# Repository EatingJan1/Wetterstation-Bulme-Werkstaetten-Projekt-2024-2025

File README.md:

# Completed school project - archived
the project continues here: https://github.com/EatingJan1/BlueRubberDuck-Weatherstation

## Wetterstation-Bulme-Werkstätten-Projekt-2024/2025

#### Outdoor-Wetterstation
Sensoren:
- BME688: xyz
- UV-Strahlung 
- Luftdruck -> easy BME680(END OF LIVE)/BME688 ist bisl besser und gleiches PINOUT und kostet nur weniger 1€ teurer
- Luftpartikel -> gehackter von Ikea(belüftet Lüfter drin)
- Temperatur -> easy BME680(END OF LIVE)/BME688 ist bisl besser und gleiches PINOUT und kostet nur weniger 1€ teurer
- Regenmenge -> Kippwage & Regenitensität über Zeit
- Windrichtung
- Windgeschwindigkeit
- Bodenfeuchtigkeit 
- UV-Strahlung Winkel -> Berechnen durch von Geolocation
- Dezibel Messung (Optional, Eher nicht)
- Höhenlage -> GPS oder Luftdruck aber zählt eher zu Berchnungen
- CO2 gehalt

##### Belüftete Sensoren  -> Mit 5V Lüfter -> ideal ohne moglichkeit ohne Lüfter
- Temperatur
- Luftfeuchtigkeit
- CO2 Gehalt
- Luftdruck
- Luftpartikel -> gehackter von Ikea (Lüfter drin) -> Teurer es zu hacken / aus zu bauen wie einen Neuen zu Kaufen

##### Berechnung:
- Taupunkt
- kWh/m2 (Sonneneinstrahlung) -> Mehrere Sensoren notwendig zu aufwendig
- gefühlte Temperatur -> Wind + Temp +Sonneneinstrahlung Vielleicht Über temperatur direkt an der gehäusewand ob eher hohe Sonneneinstrahlung oder niedrige 
- Sichtweite -> Feinstaub wichtig 
- Photovoltaik für Outdoor -> Zu viele Variablen
- Windmessung über Ultraschalwandler

##### Funk:
Übertragung: Thread

#### Mini Station:

Misst alle Daten in einem Standard Indoor Raum

Gewollte Messung:
- Temperatur
- Luftfeuchtigkeit
- CO2 Gehalt
- Luftdruck
- Helligkeit (Photowiderstand)

##### Funk:
Übertragung: Thread

#### Daten Station (HUB)
Schittstelle zu unserer Datenbank und ins Local Area Network zur überwachung der Daten

- SD Karten speicherung
- Lan anstatt Wlan
- Lan Driver
- Power über POE
- Überträgt alle Messdaten der letzen seit dem Letzten Timestamp der Datenbank einmalig pro Tag auf unseren MySQL Server. (Welche möglichkeit bzw. Daten auf mehrere Server senden)
    - Server Jan:
        - Im Falle eines Ausfall -> Selbständige Lösung, jedoch Auafall wahrscheinlichkeit höher
        - Gefahr das Daten beschädigt werden / Gelöscht
        - Komplette Administration aller Daten und des Ganzen Systems
        - Individuelle Leistung und weiterleitung (DNS)

    - Schul SQL Datenbank:
        - Keine Informationen über Systemabschaltungen (Wartungs arbeiten, Sommerferien)
        - Keine Informationen von Dauer der Daten speicherung
        - Auf System Administrator angewießen
        - Keine Leistungs bestimmung
        - Kein Eingriff ins Netzwerk
    
    - Externe SQL Server Anbieter:
        - Teuer -> Lohnt sich bei dieser Art von Projekt
        - Hohe Ausfahl Sicherheit
        - Fast keine Gefahr das Daten beschädigt werden
        - Teils auf Support angewießen.
        - Je besser die Hardware desto Teurer pro Monat wobei der Server der selbe bleibt.
        - Netzwerk Limitierungen (Aufpreise)
        - Kann von Datenlacks betroffen sein.

#### Stromversorgung für ALLE STATIONEN:
- USB C 5V -> 3,3V Step-down Converter

## Liste der Sachen für das Projekt:

### ESP's

- Router-CPU: ESP32-S3 -> Externe Antenne -> schlecht, Bessere Reichweiten Kontrolle
- Router-Thread: ESP32-H2 -> Externe Antenne -> schlecht, Bessere Reichweiten Kontrolle
- Devices: ESP32-C6 -> Externe Antenne -> schlecht, Bessere Reichweiten Kontrolle

Externe Antenne:
    https://www.mouser.at/ProductDetail/Johanson-Technology/2450AT14A0100Tqs=YCa%2FAAYMW01CU618jkZ%252BCw%3D%3D&mgh=1&vip=1&utm_id=20600977424&gad_source=1&gbraid=0AAAAADn_wf00rwxBxZh_pgnh98nrY0sxW&gclid=Cj0KCQiAhbi8BhDIARIsAJLOluei9X01ipJ_uM1vxHrcQh4ZCm8I1i5n9sgfB7ooxuq3XKT6M_dWeCkaAr6xEALw_wcB

### Sensor List:

<table>
 <tr height=20 style='height:15.0pt'>
  <td height=20 class=xl66 width=124 style='height:15.0pt;width:93pt'>Name</td>
  <td class=xl66 width=143 style='width:107pt'>Zweck</td>
  <td class=xl66 width=143 style='width:107pt'>Einheit</td>
  <td class=xl67 width=977 style='width:733pt'>&nbsp;</td>

 <tr height=20 style='height:15.0pt'>
  <td height=20 class=xl65 style='height:15.0pt'>PT 100/1000</td>
  <td class=xl65>Temperaturmessung</td>
  <td class=xl65>°C</td>
  <td></td>
 </tr>
 <tr height=20 style='height:15.0pt'>
  <td height=20 class=xl65 style='height:15.0pt'>Platine</td>
  <td class=xl65>Luftfeuchtigkeit</td>
  <td class=xl65>%</td>
  <td></td>
 </tr>
 <tr height=20 style='height:15.0pt'>
  <td height=20 class=xl65 style='height:15.0pt'>CCS811B-JOPR5K</td>
  <td class=xl65>Luftqualität</td>
  <td class=xl65>ppm</td>
  <td>https://www.digikey.at/de/products/detail/sciosense/CCS811B-JOPR5K/7428298?s=N4IgTCBcDaIMJwMoA4CMqBCBaAUgeQAUAlAVgGkQBdAXyA</td>
 </tr>
 <tr height=20 style='height:15.0pt'>
  <td height=20 class=xl65 style='height:15.0pt'>BMP280</td>
  <td class=xl65>Luftdruck</td>
  <td class=xl65>bar</td>
  <td>https://at.rs-online.com/web/p/drucksensor-ics/8496187</td>
 </tr>
 <tr height=20 style='height:15.0pt'>
  <td height=20 class=xl65 style='height:15.0pt'></td>
  <td class=xl65></td>
  <td class=xl65></td>
  <td></td>
 </tr>
 <tr height=0 style='display:none'>
  <td width=124 style='width:93pt'></td>
  <td width=143 style='width:107pt'></td>
  <td width=143 style='width:107pt'></td>
  <td width=977 style='width:733pt'></td>
 </tr>
</table>

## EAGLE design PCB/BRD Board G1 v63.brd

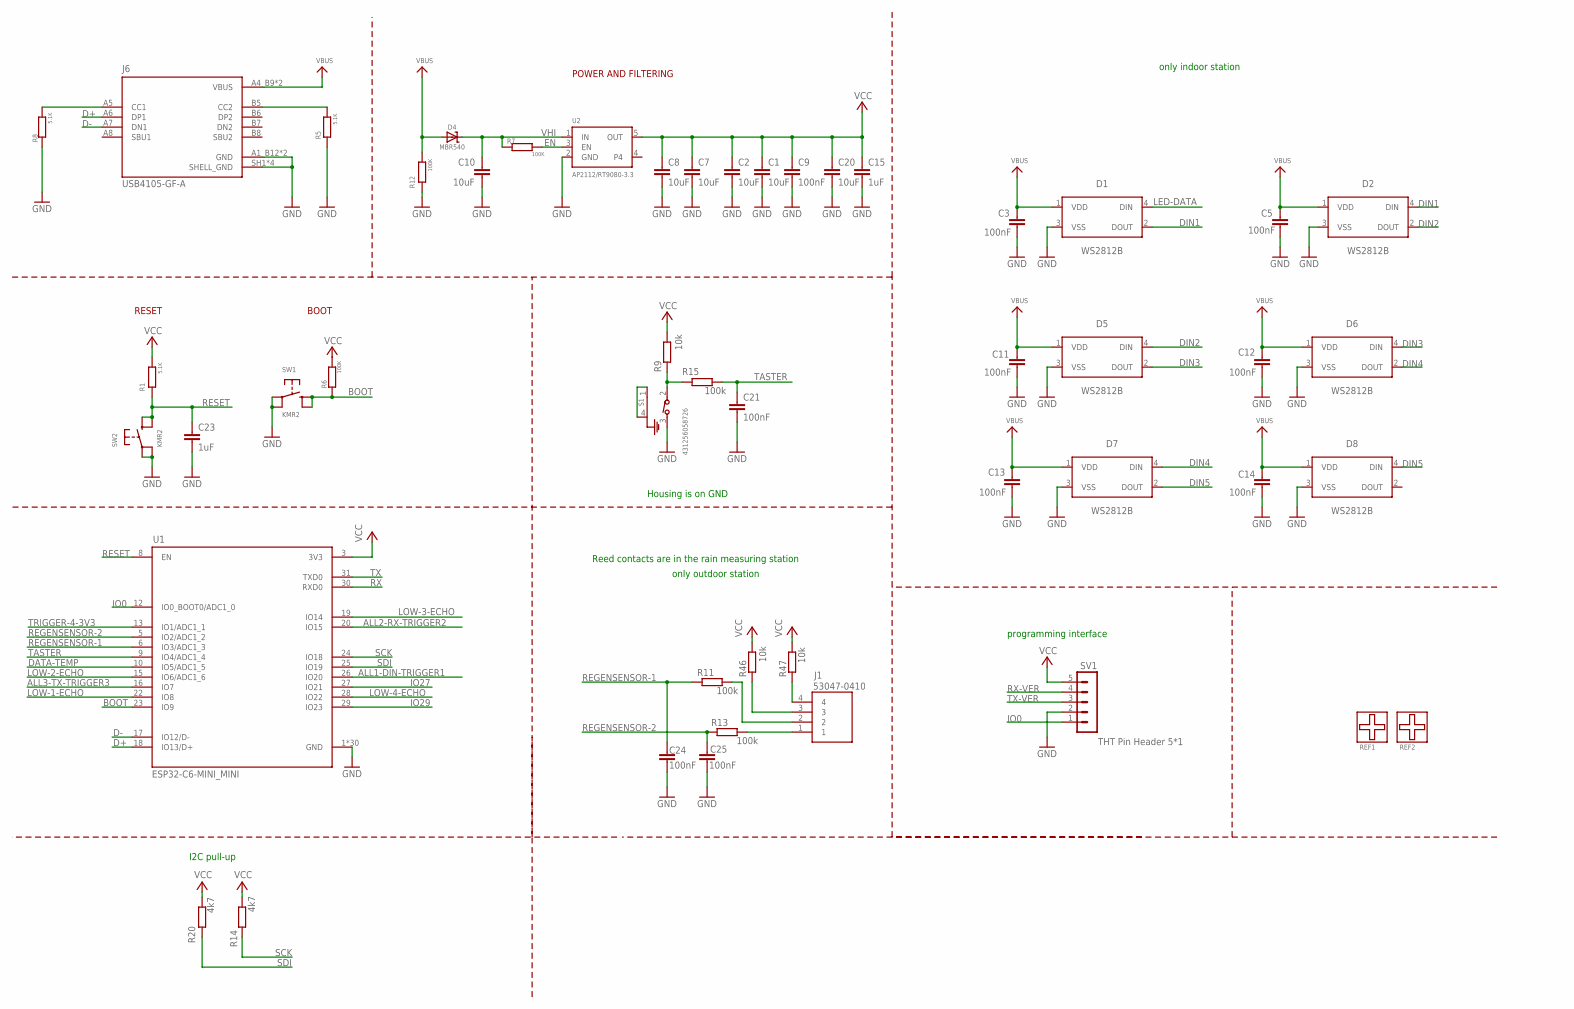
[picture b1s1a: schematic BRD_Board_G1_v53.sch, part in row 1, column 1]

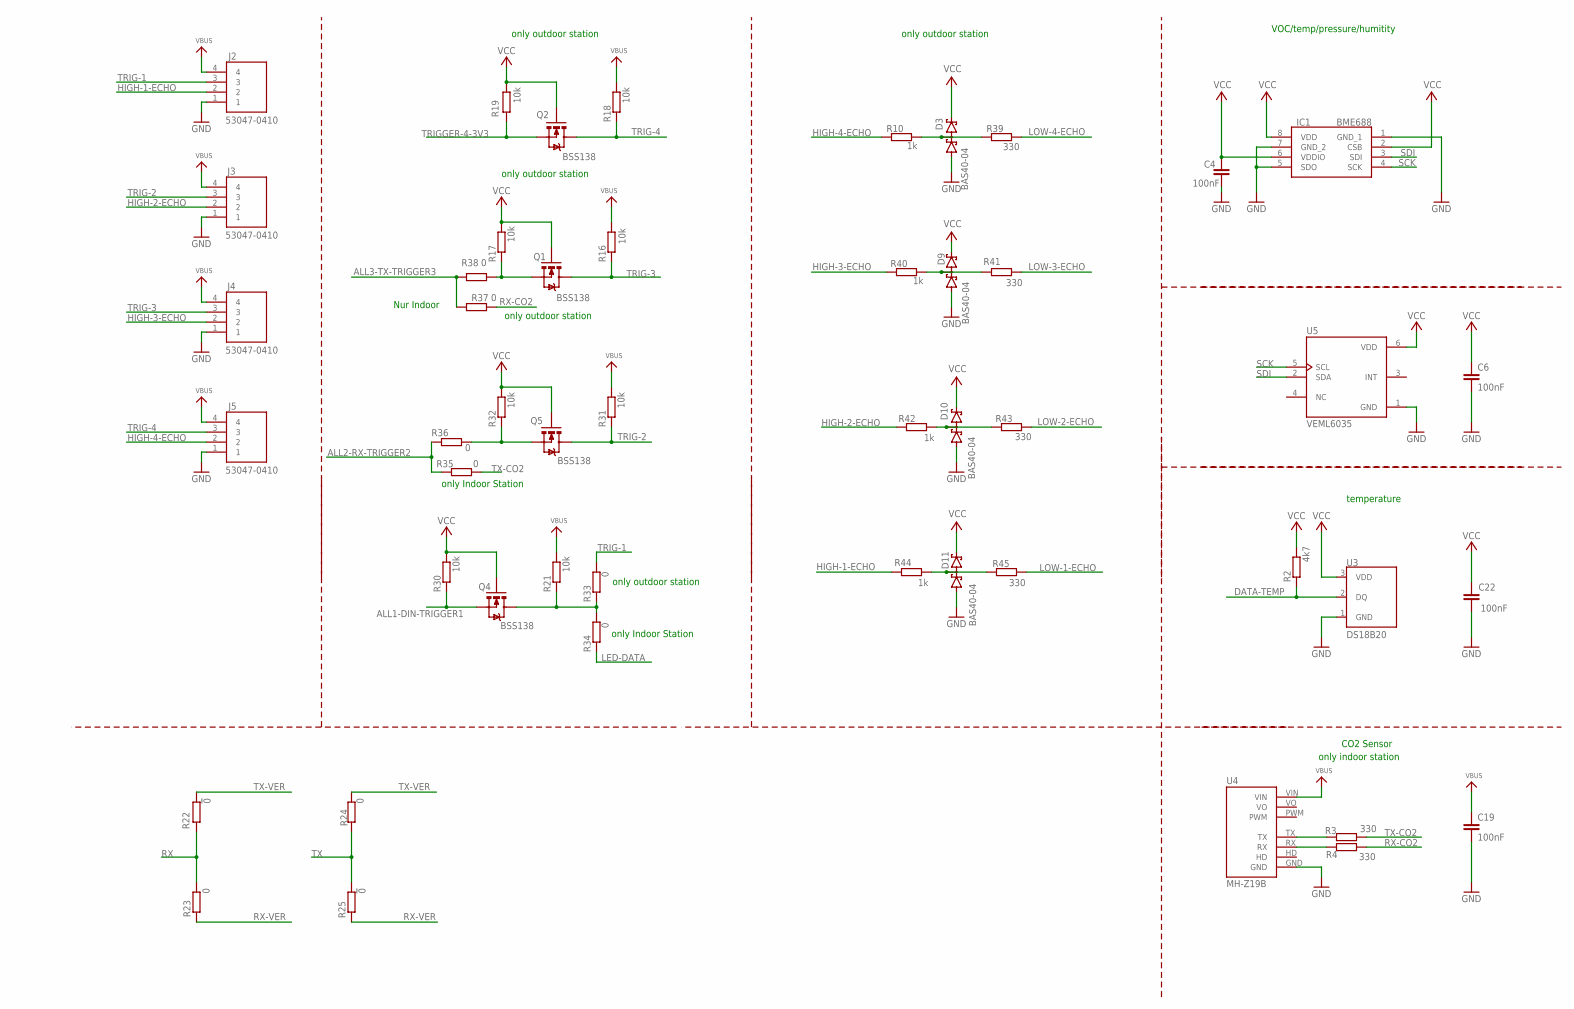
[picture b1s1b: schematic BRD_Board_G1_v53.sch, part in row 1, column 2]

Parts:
C1, C2, C7, C8, C10, C20: 10uF; C0805K
C3, C4, C5, C6, C9, C11, C12, C13, C14, C19, C21, C22, C24, C25: 100nF; C0603K
C15: 1uF; C0603K
C23: 1uF; C0805K
D1, D2, D5, D6, D7, D8: WS2812B
D3, D9, D10, D11: BAS40-04; SOT23
D4: MBR540; SOD-123
IC1: BME688
J1, J2, J3, J4, J5: 53047-0410; 530470410
J6: USB4105-GF-A; GCT_USB4105-GF-A
Q1, Q2, Q4, Q5: BSS138; SOT23
R1, R5, R8: 5.1K; R0805
R2, R14, R20: 4k7; R0805
R3, R4, R39, R41, R43, R45: 330; R0805
R6, R7, R12: 100K; R0805
R9, R16, R17, R18, R19, R21, R30, R31, R32, R46, R47: 10k; R0805
R10, R40, R42, R44: 1k; R0805
R11, R13, R15: 100k; R0805
R22, R25: !0; R0805
R23, R24, R33, R34, R35, R36, R37, R38: 0; R0805
REF1, REF2: FIDUCIALFIDU_1_3_MM; FIDU_1_3MM
S1: 431256058726; 4312560587X6
SV1: THT Pin Header 5*1; MAR05-1
SW1, SW2: KMR2; BTN_RKB2_4.6X2.8
U1: ESP32-C6-MINI_MINI; ESP32-PICO-MINI
U2: AP2112/RT9080-3.3; SOT23-5; JLC_ROTATION 0
U3: DS18B20; TO-92-AMMO
U4: MH-Z19B
U5: VEML6035; XDCR_VEML6035

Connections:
ALL1-DIN-TRIGGER1: Q4.2 (S), R30.1, U1.26 (IO20)
ALL2-RX-TRIGGER2: R35.1, R36.1, U1.20 (IO15)
ALL3-TX-TRIGGER3: R37.1, R38.1, U1.16 (IO7)
BOOT: R6.1, SW1.B (S), SW1.B' (S1), U1.23 (IO9)
D+: J6.A6 (DP1), U1.18 (IO13/D+)
D-: J6.A7 (DN1), U1.17 (IO12/D-)
DATA-TEMP: R2.1, U1.10 (IO5/ADC1_5), U3.2 (DQ)
DIN1: D1.2 (DOUT), D2.4 (DIN)
DIN2: D2.2 (DOUT), D5.4 (DIN)
DIN3: D5.2 (DOUT), D6.4 (DIN)
DIN4: D6.2 (DOUT), D7.4 (DIN)
DIN5: D7.2 (DOUT), D8.4 (DIN)
EN: R7.1, U2.3 (EN)
GND: C1.2, C2.2, C3.2, C4.1, C5.2, C6.2, C7.2, C8.2, C9.2, C10.2, C11.2, C12.2, C13.2, C14.2, C15.2, C19.2, C20.2, C21.2, C22.1, C23.2, C24.2, C25.2, D1.3 (VSS), D2.3 (VSS), D3.1 (A1), D5.3 (VSS), D6.3 (VSS), D7.3 (VSS), D8.3 (VSS), D9.1 (A1), D10.1 (A1), D11.1 (A1), IC1.1 (GND_1), IC1.5 (SDO), IC1.7 (GND_2), J2.1, J3.1, J4.1, J5.1, J6.A1_B12 (GND), J6.B1_A12 (GND), J6.SH1 (SHELL_GND), J6.SH2 (SHELL_GND), J6.SH3 (SHELL_GND), J6.SH4 (SHELL_GND), R5.1, R8.1, R12.1, S1.3, SV1.2, SW1.A, SW1.A' (P1), SW2.A, SW2.A' (P1), U1.1 (GND), U1.2 (GND), U1.11 (GND), U1.14 (GND), U1.36 (GND), U1.37 (GND), U1.38 (GND), U1.39 (GND), U1.40 (GND), U1.41 (GND), U1.42 (GND), U1.43 (GND), U1.44 (GND), U1.45 (GND), U1.46 (GND), U1.47 (GND), U1.48 (GND), U1.49 (GND), U1.50 (GND), U1.51 (GND), U1.52 (GND), U1.53 (GND), U1.54 (GND), U1.55 (GND), U1.56 (GND), U1.57 (GND), U1.58 (GND), U1.59 (GND), U1.60 (GND), U1.61 (GND), U2.2 (GND), U3.1 (GND), U4.GND, U5.1 (GND)
HIGH-1-ECHO: J2.2, R44.2
HIGH-2-ECHO: J3.2, R42.2
HIGH-3-ECHO: J4.2, R40.2
HIGH-4-ECHO: J5.2, R10.2
IO0: SV1.1, U1.12 (IO0_BOOT0/ADC1_0)
IO27: U1.27 (IO21)
IO29: U1.29 (IO23)
LED-DATA: D1.4 (DIN), R34.1
LOW-1-ECHO: R45.1, U1.22 (IO8)
LOW-2-ECHO: R43.1, U1.15 (IO6/ADC1_6)
LOW-3-ECHO: R41.1, U1.19 (IO14)
LOW-4-ECHO: R39.1, U1.28 (IO22)
unnamed: R4.2, U4.RX
unnamed: R9.1, R15.2, S1.2
unnamed: R3.2, U4.TX
unnamed: S1.1 (GND1), S1.4 (GND)
unnamed: D3.3 (C1A2), R10.1, R39.2
unnamed: D9.3 (C1A2), R40.1, R41.2
unnamed: Q1.2 (S), R17.1, R38.2
unnamed: J6.A5 (CC1), R8.2
unnamed: J6.B5 (CC2), R5.2
unnamed: D10.3 (C1A2), R42.1, R43.2
unnamed: D11.3 (C1A2), R44.1, R45.2
unnamed: J1.3, R46.1
unnamed: J1.4, R47.1
unnamed: Q5.2 (S), R32.1, R36.2
unnamed: Q4.3 (D), R21.1, R33.1, R34.2
unnamed: J1.2, R11.1
unnamed: J1.1, R13.1
REGENSENSOR-1: C24.1, R11.2, U1.6 (IO3/ADC1_3)
REGENSENSOR-2: C25.1, R13.2, U1.5 (IO2/ADC1_2)
RESET: C23.1, R1.1, SW2.B (S), SW2.B' (S1), U1.8 (EN)
RX: R22.2, R23.1, U1.30 (RXD0)
RX-CO2: R4.1, R37.2
RX-VER: R23.2, R25.2, SV1.4
SCK: IC1.4 (SCK), R14.1, U1.24 (IO18), U5.5 (SCL)
SDI: IC1.3 (SDI), R20.1, U1.25 (IO19), U5.2 (SDA)
TASTER: C21.1, R15.1, U1.9 (IO4/ADC1_4)
TRIG-1: J2.3, R33.2
TRIG-2: J3.3, Q5.3 (D), R31.1
TRIG-3: J4.3, Q1.3 (D), R16.1
TRIG-4: J5.3, Q2.3 (D), R18.1
TRIGGER-4-3V3: Q2.2 (S), R19.1, U1.13 (IO1/ADC1_1)
TX: R24.2, R25.1, U1.31 (TXD0)
TX-CO2: R3.1, R35.2
TX-VER: R22.1, R24.1, SV1.3
VBUS: C3.1, C5.1, C11.1, C12.1, C13.1, C14.1, C19.1, D1.1 (VDD), D2.1 (VDD), D4.A, D5.1 (VDD), D6.1 (VDD), D7.1 (VDD), D8.1 (VDD), J2.4, J3.4, J4.4, J5.4, J6.A4_B9 (VBUS), J6.B4_A9 (VBUS), R12.2, R16.2, R18.2, R21.2, R31.2, U4.VIN
VCC: C1.1, C2.1, C4.2, C6.1, C7.1, C8.1, C9.1, C15.1, C20.1, C22.2, D3.2 (C2), D9.2 (C2), D10.2 (C2), D11.2 (C2), IC1.2 (CSB), IC1.6 (VDDIO), IC1.8 (VDD), Q1.1 (G), Q2.1 (G), Q4.1 (G), Q5.1 (G), R1.2, R2.2, R6.2, R9.2, R14.2, R17.2, R19.2, R20.2, R30.2, R32.2, R46.2, R47.2, SV1.5, U1.3 (3V3), U2.5 (OUT), U3.3 (VDD), U5.6 (VDD)
VHI: C10.1, D4.C, R7.2, U2.1 (IN)

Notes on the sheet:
POWER AND FILTERING
RESET
CO2 Sensor
temperature
VOC/temp/pressure/humitity
Reed contacts are in the rain measuring station
programming interface
Housing is on GND
only indoor station
only outdoor station
Nur Indoor
only Indoor Station
BOOT
I2C pull-up

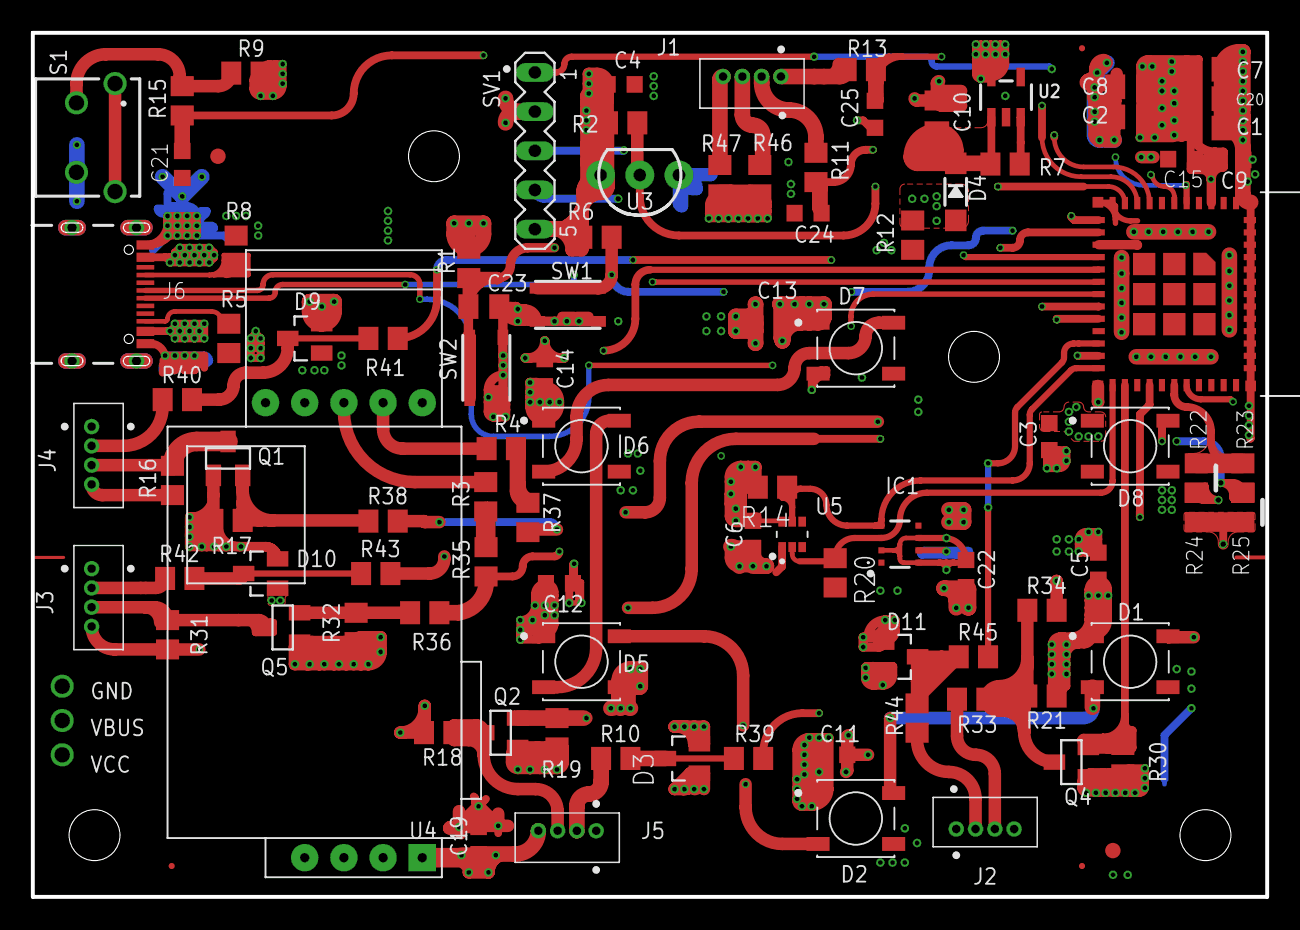
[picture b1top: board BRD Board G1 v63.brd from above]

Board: 4 copper layers, 80.0 x 56.0 mm, 98 parts (0 on the bottom side), 61 nets.

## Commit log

2024-12-09 Update README.md
    Change - to ae
2024-12-09 Update README.md
    Add Liste and ESP List
2024-12-09 Update README.md
    Readme add: Ideen
2024-12-09 Update README.md
    Readme Change Format
2024-12-09 Update README.md
    Readme add Sensorlist
2024-12-09 Add Esp32-S3 -> README.md
2024-12-12 Update README.md
    Add Thread
2024-12-12 Update README.md
    Change Layout
2024-12-12 Update README.md
    Add useful Links
2024-12-14 Update README.md
    Stromversorgung :
    - USB C
2024-12-16 Update README.md
    Add ESP Blogs
2024-12-17 Add "Blockschaltbild" to powerpoint
2024-12-17 Bauteilbeschreibung anfang
2024-12-17 Add "Blockschaltbild" to Vorstellung
2024-12-17 Change Vorstellung
2024-12-17 Update Powerpoint
2024-12-17 Add PDF Vorstellung
2024-12-25 Update README.md
    Antennen
2024-12-25 Update README.md
    Luftpartikel
2025-01-06 Update README.md
    Add Thread Netzwerk
2025-01-06 Update README.md
    Add Helligkeit to Mini Station
2025-01-08 Update README.md
    Add link to Thread Netzwerk
2025-01-08 Move Vorstellung.pdf & Vorstellung.pptx into /Presentation
2025-01-08 Add .gitignore
2025-01-20 Move BME688.sch in Schaltplan und Layouts
2025-01-20 Update README.md
    Add Antenne Link
2025-01-22 Add Indoor.md
2025-01-22 Change Guidline-Indoor.md
2025-01-25 Footprint vom ESP32-H2-MINI-1U
    Pins sollten richtig sein muss nur noch wer doppelt überprüfen
2025-01-26 jetzt passen die Footprints vom esp32
    vorher VIAs die aus nem unbekannten Grund zu Groß geworden sind und ich nicht verkleinern konnte.
2025-01-26 Delete Schaltplan und Layouts/Esp32-H2-wroom-u1-Nx.sch
    Da falsch
2025-01-26 Delete Schaltplan und Layouts/ESP32-H2-MINI-1-H2-Pinbelegung-richtig.lbr
    Da falsch
2025-01-26 Software Ordner import
2025-01-27 temp Test erstellt
2025-01-27 Verbesserung -CHAT- Programm Test DHT11
2025-01-27 Qr Code Gen add
2025-01-29 3V3 STEP DOWN CONVERTER
2025-01-29 SCHlatplan des 3V3 Step down converter
2025-02-11 Matter Specification
2025-03-11 Stütze
2025-03-11 Add Outdoorwetter
2025-03-11 Add Stuetze
2025-03-11 Add Wippe
2025-03-11 Stütze v2
2025-03-25 Schaltplan fertig wahrscheinlich
2025-05-13 Add 2 partitions for ESP32; use Matter on 4M Flash
2025-05-20 Move folder
2025-05-20 Add Patition readme
2025-06-03 average_per_time
2025-06-03 Matter Docu
2025-06-15 Change PCB
2025-06-15 Update 3d
2025-06-16 Change Outdoor
2025-06-16 CHange Modle
2025-06-19 add scr
2025-06-19 change average_per_time folder
2025-06-19 rm Doc
2025-06-19 add pptx
2025-06-19 add gitig
2025-06-19 change folder
2025-06-19 rm MCHyetometer-REED
2025-06-19 Add Submodule MCHyetometer-REED
2025-06-19 change to new lib
2025-06-19 rm Anemometer lib
2025-06-19 Add Submodule MCAnemometer-Ultrasonic
2025-06-19 Update main to new Anemometer lib
2025-06-19 rm Matter
2025-06-19 Add Submodule 2x Matter
2025-06-19 Change lib for Matter
2025-06-19 newest Libs
2025-06-19 rm LEDanimation lib
2025-06-19 Add Submodule NeoPixel-Animation-lib
2025-06-19 Changes for new led lib
2025-06-20 rm .vscode
2025-06-20 add vscode to gitignore
2025-06-20 move readme
2025-06-20 Add Documentation
2025-06-26 Update main.cpp to last version
2025-06-26 Update 3D Versions

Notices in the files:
parts and their libraries:
microbuilder: This work is placed in the public domain, and may be freely used for commercial and non-commercial work with the following conditions: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
SparkFun-Sensors: Licensing: Creative Commons ShareAlike 4.0 International - https://creativecommons.org/licenses/by-sa/4.0
